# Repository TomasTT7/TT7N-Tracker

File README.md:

# TT7N-Tracker
This is the main repository for TT7N, a two band superpressure balloon tracker. It includes the board and schematic design files for Eagle, and the current firmware.

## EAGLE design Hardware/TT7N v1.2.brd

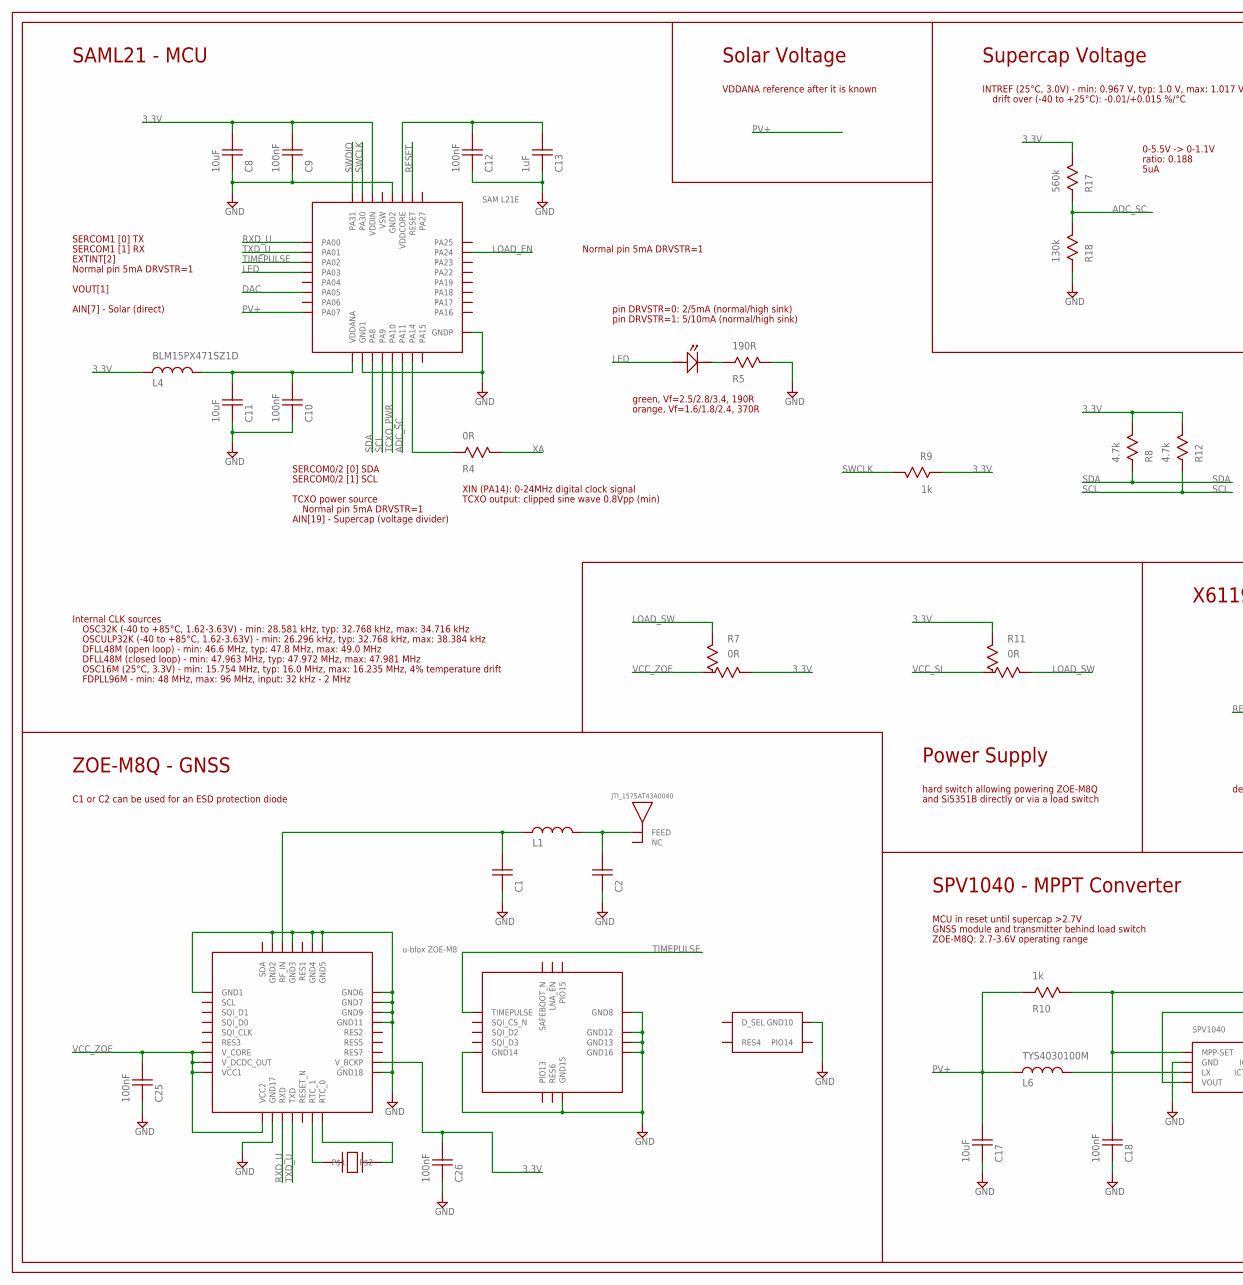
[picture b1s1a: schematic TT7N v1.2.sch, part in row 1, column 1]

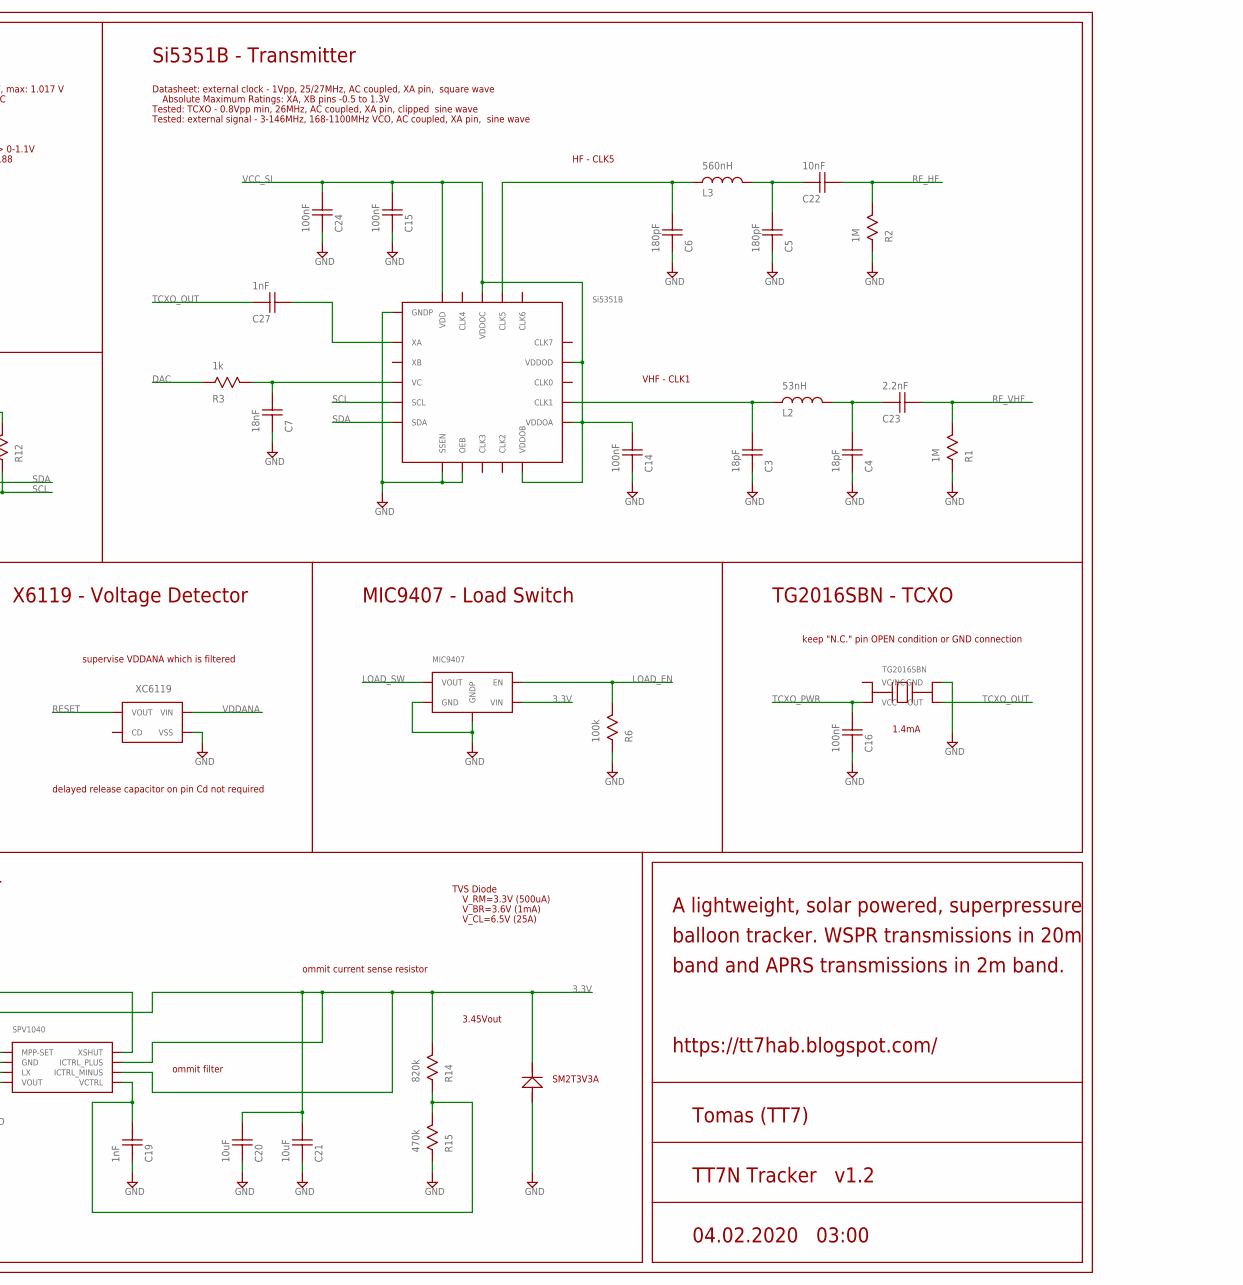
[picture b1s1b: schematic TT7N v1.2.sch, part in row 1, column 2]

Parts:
ANT1: JTI_1575AT43A0040
C1, C2: CAP0402
C3, C4: 18pF; CAP0402
C5, C6: 180pF; CAP0402
C7: 18nF; CAP0402
C8, C11, C17, C20, C21: 10uF; CAP0402
C9, C10, C12, C14, C15, C16, C18, C24, C25, C26: 100nF; CAP0402
C13: 1uF; CAP0402
C19, C27: 1nF; CAP0402
C22: 10nF; CAP0402
C23: 2.2nF; CAP0402
D1: SM2T3V3A
L1: IND0402
L2: 53nH; IND0402
L3: 560nH; IND0402
L4: BLM15PX471SZ1D; IND0402
L6: TYS4030100M
LED1: LED0603
R1, R2: 1M; RES0402
R3, R9, R10: 1k; RES0402
R4: 0R; RES0402
R5: 190R; RES0402
R6: 100k; RES0402
R7, R11: 0R; RES0402-3
R8, R12: 4.7k; RES0402
R14: 820k; RES0402
R15: 470k; RES0402
R17: 560k; RES0402
R18: 130k; RES0402
TCXO1: TG2016SBN
U1: SPV1040
U2: SAML21E18B-MUT
U3: XC6119
U4: UBLOX_ZOE-M8
U5: SI5351B
U6: MIC9407
U7: CM8V-T1A

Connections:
3.3V: C8.P$2, C9.P$2, C20.P$2, C21.P$2, C26.P$2, D1.CATHODE, L4.P$1, R7.3, R8.P$2, R9.P$1, R11.1, R12.P$2, R14.P$2, R17.P$2, U1.ICTRL_MINUS, U1.ICTRL_PLUS, U1.VOUT, U2.VDDIN, U4.V_BCKP, U6.VIN
ADC_SC: R17.P$1, R18.P$2, U2.PA11
CLK1: C3.P$2, L2.P$1, U5.CLK1
CLK5: C6.P$2, L3.P$1, U5.CLK5
DAC: R3.P$1, U2.PA05
GND: C1.P$1, C2.P$1, C3.P$1, C4.P$1, C5.P$1, C6.P$1, C7.P$1, C8.P$1, C9.P$1, C10.P$1, C11.P$1, C12.P$1, C13.P$1, C14.P$1, C15.P$1, C16.P$1, C17.P$1, C18.P$1, C19.P$1, C20.P$1, C21.P$1, C24.P$1, C25.P$1, C26.P$1, D1.ANODE, R1.P$1, R2.P$1, R5.P$2, R6.P$1, R15.P$1, R18.P$1, TCXO1.GND, U1.GND, U2.GND1, U2.GND2, U2.GNDP, U3.VSS, U4.GND1, U4.GND2, U4.GND3, U4.GND4, U4.GND5, U4.GND6, U4.GND7, U4.GND8, U4.GND9, U4.GND10, U4.GND11, U4.GND12, U4.GND13, U4.GND14, U4.GND15, U4.GND16, U4.GND17, U4.GND18, U5.GNDP, U5.OEB, U5.SSEN, U6.GND, U6.GNDP
LED: LED1.ANODE, U2.PA03
LOAD_EN: R6.P$2, U2.PA24, U6.EN
LOAD_SW: R7.1, R11.3, U6.VOUT
unnamed: C7.P$2, R3.P$2, U5.VC
unnamed: R4.P$1, U2.PA14
unnamed: LED1.CATHODE, R5.P$1
unnamed: U4.RTC_0, U7.P$2
unnamed: C12.P$2, C13.P$2, U2.VDDCORE
unnamed: L6.P2, U1.LX
unnamed: C5.P$2, C22.P$1, L3.P$2
unnamed: C18.P$2, R10.P$2, U1.MPP-SET, U1.XSHUT
unnamed: C19.P$2, R14.P$1, R15.P$2, U1.VCTRL
unnamed: U4.RTC_1, U7.P$1
unnamed: C4.P$2, C23.P$1, L2.P$2
PV+: C17.P$2, L6.P1, R10.P$1, U2.PA07
RESET: U2.RESET, U3.VOUT
RF_HF: C22.P$2, R2.P$2
RF_IN: C1.P$2, L1.P$1, U4.RF_IN
RF_UHF: ANT1.FEED, C2.P$2, L1.P$2
RF_VHF: C23.P$2, R1.P$2
RXD_U: U2.PA00, U4.RXD
SCL: R12.P$1, U2.PA09 (PA9), U5.SCL
SDA: R8.P$1, U2.PA08 (PA8), U5.SDA
SWCLK: R9.P$2, U2.PA30
SWDIO: U2.PA31
TCXO_OUT: C27.P$1, TCXO1.OUT
TCXO_PWR: C16.P$2, TCXO1.VCC, U2.PA10
TIMEPULSE: U2.PA02, U4.TIMEPULSE
TXD_U: U2.PA01, U4.TXD
VCC_SI: C14.P$2, C15.P$2, C24.P$2, R11.2, U5.VDD, U5.VDDOA, U5.VDDOB, U5.VDDOC, U5.VDDOD
VCC_ZOE: C25.P$2, R7.2, U4.VCC1, U4.VCC2, U4.V_CORE, U4.V_DCDC_OUT
VDDANA: C10.P$2, C11.P$2, L4.P$2, U2.VDDANA, U3.VIN
XA: C27.P$2, R4.P$2, U5.XA

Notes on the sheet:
pin DRVSTR=0: 2/5mA (normal/high sink)
pin DRVSTR=1: 5/10mA (normal/high sink)
C1 or C2 can be used for an ESD protection diode
green, Vf=2.5/2.8/3.4, 190R
HF - CLK5
VHF - CLK1
MCU in reset until supercap >2.7V
GNSS module and transmitter behind load switch
ZOE-M8Q: 2.7-3.6V operating range
1.4mA
ZOE-M8Q - GNSS
Si5351B - Transmitter
XIN (PA14): 0-24MHz digital clock signal
SPV1040 - MPPT Converter
SAML21 - MCU
ommit filter
3.45Vout
keep "N.C." pin OPEN condition or GND connection
ommit current sense resistor
https://tt7hab.blogspot.com/
TG2016SBN - TCXO
MIC9407 - Load Switch
X6119 - Voltage Detector
supervise VDDANA which is filtered
SERCOM0/2 [0] SDA
SERCOM0/2 [1] SCL
SERCOM1 [0] TX
SERCOM1 [1] RX
VOUT[1]
Normal pin 5mA DRVSTR=1
delayed release capacitor on pin Cd not required
TVS Diode
SM2T3V3A
V_RM=3.3V (500uA)
V_BR=3.6V (1mA)
V_CL=6.5V (25A)
TCXO output: clipped sine wave 0.8Vpp (min)
Solar Voltage
Supercap Voltage
Tomas (TT7)

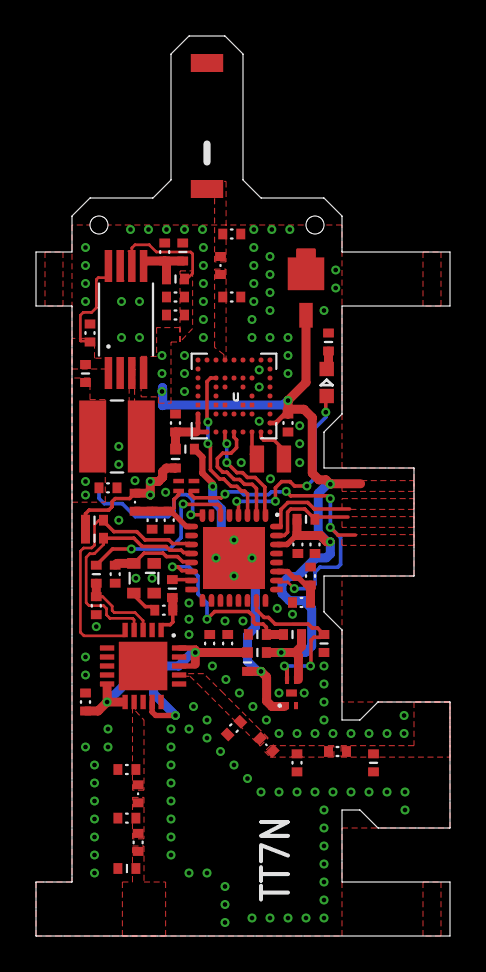
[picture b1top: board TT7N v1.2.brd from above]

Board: 2 copper layers, 23.0 x 50.0 mm, 59 parts (0 on the bottom side), 38 nets.

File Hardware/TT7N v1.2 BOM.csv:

"Part";"Value";"Device";"Package";"Description";"";
"ANT1";"JTI_1575AT43A0040";"JTI_1575AT43A0040";"JTI_1575AT43A0040";"JTI_1575AT43A0040 GNSS antenna footprint.";"";
"C1";"";"CAP0402";"CAP0402";"CAPACITOR 0402 - 1 x 0.5 x 0.35mm";"";
"C2";"";"CAP0402";"CAP0402";"CAPACITOR 0402 - 1 x 0.5 x 0.35mm";"";
"C3";"18pF";"CAP0402";"CAP0402";"CAPACITOR 0402 - 1 x 0.5 x 0.35mm";"";
"C4";"18pF";"CAP0402";"CAP0402";"CAPACITOR 0402 - 1 x 0.5 x 0.35mm";"";
"C5";"180pF";"CAP0402";"CAP0402";"CAPACITOR 0402 - 1 x 0.5 x 0.35mm";"";
"C6";"180pF";"CAP0402";"CAP0402";"CAPACITOR 0402 - 1 x 0.5 x 0.35mm";"";
"C7";"18nF";"CAP0402";"CAP0402";"CAPACITOR 0402 - 1 x 0.5 x 0.35mm";"";
"C8";"10uF";"CAP0402";"CAP0402";"CAPACITOR 0402 - 1 x 0.5 x 0.35mm";"";
"C9";"100nF";"CAP0402";"CAP0402";"CAPACITOR 0402 - 1 x 0.5 x 0.35mm";"";
"C10";"100nF";"CAP0402";"CAP0402";"CAPACITOR 0402 - 1 x 0.5 x 0.35mm";"";
"C11";"10uF";"CAP0402";"CAP0402";"CAPACITOR 0402 - 1 x 0.5 x 0.35mm";"";
"C12";"100nF";"CAP0402";"CAP0402";"CAPACITOR 0402 - 1 x 0.5 x 0.35mm";"";
"C13";"1uF";"CAP0402";"CAP0402";"CAPACITOR 0402 - 1 x 0.5 x 0.35mm";"";
"C14";"100nF";"CAP0402";"CAP0402";"CAPACITOR 0402 - 1 x 0.5 x 0.35mm";"";
"C15";"100nF";"CAP0402";"CAP0402";"CAPACITOR 0402 - 1 x 0.5 x 0.35mm";"";
"C16";"100nF";"CAP0402";"CAP0402";"CAPACITOR 0402 - 1 x 0.5 x 0.35mm";"";
"C17";"10uF";"CAP0402";"CAP0402";"CAPACITOR 0402 - 1 x 0.5 x 0.35mm";"";
"C18";"100nF";"CAP0402";"CAP0402";"CAPACITOR 0402 - 1 x 0.5 x 0.35mm";"";
"C19";"1nF";"CAP0402";"CAP0402";"CAPACITOR 0402 - 1 x 0.5 x 0.35mm";"";
"C20";"10uF";"CAP0402";"CAP0402";"CAPACITOR 0402 - 1 x 0.5 x 0.35mm";"";
"C21";"10uF";"CAP0402";"CAP0402";"CAPACITOR 0402 - 1 x 0.5 x 0.35mm";"";
"C22";"10nF";"CAP0402";"CAP0402";"CAPACITOR 0402 - 1 x 0.5 x 0.35mm";"";
"C23";"2.2nF";"CAP0402";"CAP0402";"CAPACITOR 0402 - 1 x 0.5 x 0.35mm";"";
"C24";"100nF";"CAP0402";"CAP0402";"CAPACITOR 0402 - 1 x 0.5 x 0.35mm";"";
"C25";"100nF";"CAP0402";"CAP0402";"CAPACITOR 0402 - 1 x 0.5 x 0.35mm";"";
"C26";"100nF";"CAP0402";"CAP0402";"CAPACITOR 0402 - 1 x 0.5 x 0.35mm";"";
"C27";"1nF";"CAP0402";"CAP0402";"CAPACITOR 0402 - 1 x 0.5 x 0.35mm";"";
"D1";"SM2T3V3A";"SM2T3V3A";"SM2T3V3A";"SM2T3V3A TVS diode footprint";"";
"L1";"";"IND0402";"IND0402";"INDUCTOR 0402 - 1 x 0.5 x 0.35mm";"";
"L2";"53nH";"IND0402";"IND0402";"INDUCTOR 0402 - 1 x 0.5 x 0.35mm";"";
"L3";"560nH";"IND0402";"IND0402";"INDUCTOR 0402 - 1 x 0.5 x 0.35mm";"";
"L4";"BLM15PX471SZ1D";"IND0402";"IND0402";"INDUCTOR 0402 - 1 x 0.5 x 0.35mm";"";
"L6";"TYS4030100M";"TYS4030100M";"TYS4030100M";"TYS4030100M inductor footprint.";"";
"LED1";"LED0603";"LED0603";"LED0603";"LED 0603";"";
"R1";"1M";"RES0402";"RES0402";"RESISTOR 0402 - 1 x 0.5 x 0.35mm";"";
"R2";"1M";"RES0402";"RES0402";"RESISTOR 0402 - 1 x 0.5 x 0.35mm";"";
"R3";"1k";"RES0402";"RES0402";"RESISTOR 0402 - 1 x 0.5 x 0.35mm";"";
"R4";"0R";"RES0402";"RES0402";"RESISTOR 0402 - 1 x 0.5 x 0.35mm";"";
"R5";"190R";"RES0402";"RES0402";"RESISTOR 0402 - 1 x 0.5 x 0.35mm";"";
"R6";"100k";"RES0402";"RES0402";"RESISTOR 0402 - 1 x 0.5 x 0.35mm";"";
"R7";"0R";"RES0402-3";"RES0402-3";"Resistor Switch.";"";
"R8";"4.7k";"RES0402";"RES0402";"RESISTOR 0402 - 1 x 0.5 x 0.35mm";"";
"R9";"1k";"RES0402";"RES0402";"RESISTOR 0402 - 1 x 0.5 x 0.35mm";"";
"R10";"1k";"RES0402";"RES0402";"RESISTOR 0402 - 1 x 0.5 x 0.35mm";"";
"R11";"0R";"RES0402-3";"RES0402-3";"Resistor Switch.";"";
"R12";"4.7k";"RES0402";"RES0402";"RESISTOR 0402 - 1 x 0.5 x 0.35mm";"";
"R14";"820k";"RES0402";"RES0402";"RESISTOR 0402 - 1 x 0.5 x 0.35mm";"";
"R15";"470k";"RES0402";"RES0402";"RESISTOR 0402 - 1 x 0.5 x 0.35mm";"";
"R17";"560k";"RES0402";"RES0402";"RESISTOR 0402 - 1 x 0.5 x 0.35mm";"";
"R18";"130k";"RES0402";"RES0402";"RESISTOR 0402 - 1 x 0.5 x 0.35mm";"";
"TCXO1";"TG2016SBN";"TG2016SBN";"TG2016SBN";"TG2016SBN TCXO in a 2.0x1.6mm package.";"";
"U1";"SPV1040";"SPV1040";"SPV1040";"SPV1040 high efficiency solar battery charger with embedded MPPT in a TSSOP8 package.";"";
"U2";"SAML21E18B-MUT";"SAML21E18B-MUT";"SAML21E18B-MUT";"Atmel's SAM L21E18B in a 32 pin QFN package.";"";
"U3";"XC6119";"XC6119";"XC6119";"XC6119 supervisor IC in a USPN-4 package.";"";
"U4";"UBLOX_ZOE-M8";"UBLOX_ZOE-M8";"UBLOX_ZOE-M8";"U-blox ZOE-M8 footprint.";"";
"U5";"SI5351B";"SI5351B";"SI5351B";"Si5351B transmitter.";"";
"U6";"MIC9407";"MIC9407";"MIC9407";"MIC9407 load switch in MLF package footprint.";"";
"U7";"CM8V-T1A";"CM8V-T1A";"CM8V-T1A";"CM8V-T1A 32.768kHz crystal footprint.";"";

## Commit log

2020-02-05 Create temp
